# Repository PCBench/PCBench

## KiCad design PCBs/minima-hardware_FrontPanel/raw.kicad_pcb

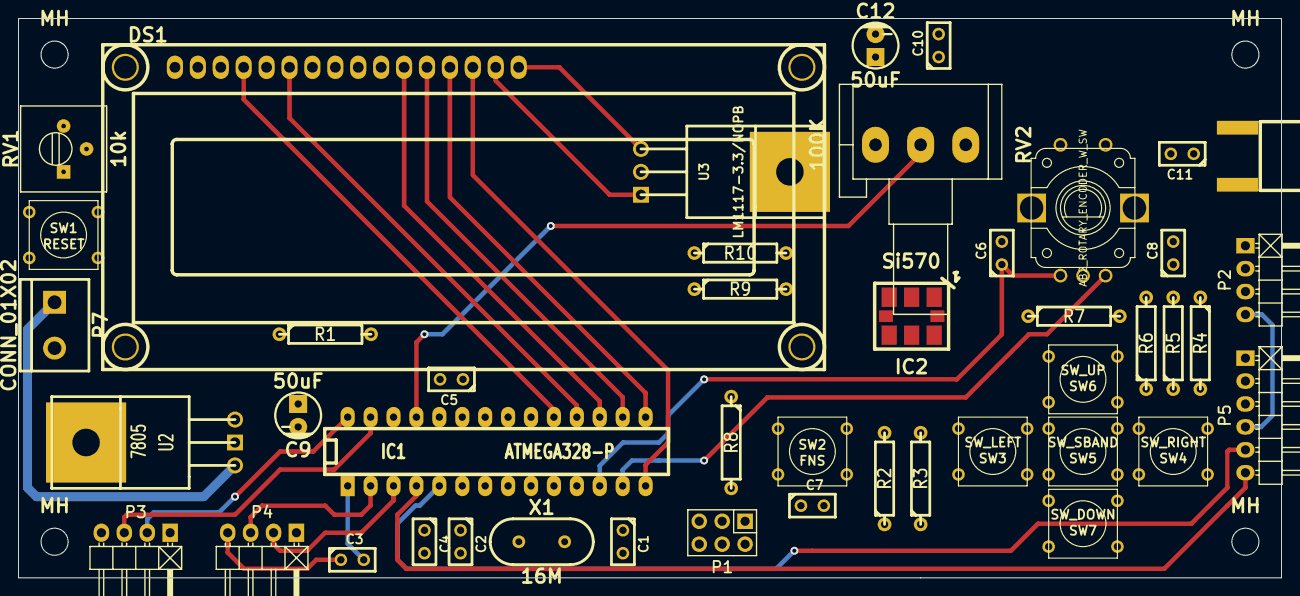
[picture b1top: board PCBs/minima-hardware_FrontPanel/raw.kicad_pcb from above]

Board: 2 copper layers, 140.0 x 62.0 mm, 49 parts (0 on the bottom side), 39 nets.

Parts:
C1, C2: 22pF; C1
C3: 0.1; C1
C4, C5: C; C1
C6, C7, C8: 1nF; C1
C9, C12: 50uF; Capacitor5x6RM2.5
C10, C11: .1uF; C1
DS1: LCD16X2; WC1602A
IC1: ATMEGA328-P; DIP-28__300_ELL
IC2: Si570; SI570_SI571_Standard
J1: sma; SMA_EDGE
MH: MountingHole_3mm_RevA_Date21Jun2010; MountingHole_3mm
MH#2, MH#3, MH#4: MountingHole_3mm_RevA_Date21Jun2010; MountingHole_3mm
P1: ICSP; Pin_Header_Straight_2x03
P2, P3, P4: CONN_01X04; Pin_Header_Angled_1x04
P5: CONN_01X06; Pin_Header_Angled_1x06
P7: CONN_01X02; bornier2
R1: 100K; R4
R2, R3, R4, R5, R6, R7: 4.7k; R4
R8: 47k; R4
R9, R10: 4.7K; R4
ROT_ENC1: AB2_ROTARY_ENCODER_W_SW; AB2_ROTARY_ENCODER_W_SWITCH
RV1: 10k; Potentiometer_Trimmer-Suntan-TSR-3386P
RV2: 100K; Potentiometer_Alps-RK16-single_largePads
SW1: RESET; SW_PUSH_SMALL
SW2: FNS; SW_PUSH_SMALL
SW3: SW_LEFT; SW_PUSH_SMALL
SW4: SW_RIGHT; SW_PUSH_SMALL
SW5: SW_SBAND; SW_PUSH_SMALL
SW6: SW_UP; SW_PUSH_SMALL
SW7: SW_DOWN; SW_PUSH_SMALL
U2: 7805; LM78XX
U3: LM1117-3.3/NOPB; TO220
X1: 16M; HC-49V

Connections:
+3.3V: C10.1, C12.1, IC2.6, P3.4, R9.1, R10.1, U3.3
+12V: P7.1, U2.VI
/D4: DS1.11, IC1.17, P1.4
/D5: DS1.12, IC1.16
/D6: DS1.13, IC1.15
/D7: DS1.14, IC1.14
/E: DS1.6, IC1.18, P1.1
/RS: DS1.4, IC1.19, P1.3
/TUNE: IC1.25, RV2.2
CWTONE: IC1.5, P5.5
GND: C1.2, C2.2, C4.2, C5.2, C6.2, C7.2, C8.2, C9.2, C10.2, C12.2, DS1.1, DS1.5, DS1.16, IC1.8, IC1.22, IC2.3, IC2.5, J1.2, P1.6, P2.1, P3.1, P4.1, P5.1, P7.2, ROT_ENC1.2, ROT_ENC1.4, RV1.1, RV2.1, SW1.2, SW2.2, SW3.2, SW4.2, SW5.2, SW6.2, SW7.2, U2.GND, U3.2
KEY: IC1.24, P5.2
unnamed: C1.1, IC1.10, X1.2
unnamed: C2.1, IC1.9, X1.1
unnamed: C3.2, IC1.1, P1.5, SW1.1
unnamed: C5.1, IC1.20, R1.2
unnamed: C6.1, IC1.12, ROT_ENC1.1
unnamed: C7.1, IC1.26, R2.2, R8.1, SW2.1
unnamed: C8.1, IC1.13, ROT_ENC1.3
unnamed: C11.1, J1.1
unnamed: C11.2, IC2.4
unnamed: DS1.3, RV1.2
unnamed: IC1.21, R8.2
unnamed: R2.1, R3.2, SW3.1
unnamed: R3.1, R4.2, SW4.1
unnamed: R4.1, R5.2, SW5.1
unnamed: R5.1, R6.2, SW6.1
unnamed: R6.1, R7.2, SW7.1
unnamed: R7.1, ROT_ENC1.6
PTT: IC1.23, P5.3
RF386: IC1.11, P2.3
RTS: C3.1, P4.4
RX: IC1.3, P4.2
SCL: IC1.28, IC2.8, P3.2, R10.2
SDA: IC1.27, IC2.7, P3.3, R9.2
TX: IC1.2, P4.3
TX/RX: IC1.6, P2.4, P5.4
USB/LSB: IC1.4, P5.6
VCC: C4.1, C9.1, DS1.2, DS1.15, IC1.7, P1.2, R1.1, RV1.3, RV2.3, U2.VO, U3.1

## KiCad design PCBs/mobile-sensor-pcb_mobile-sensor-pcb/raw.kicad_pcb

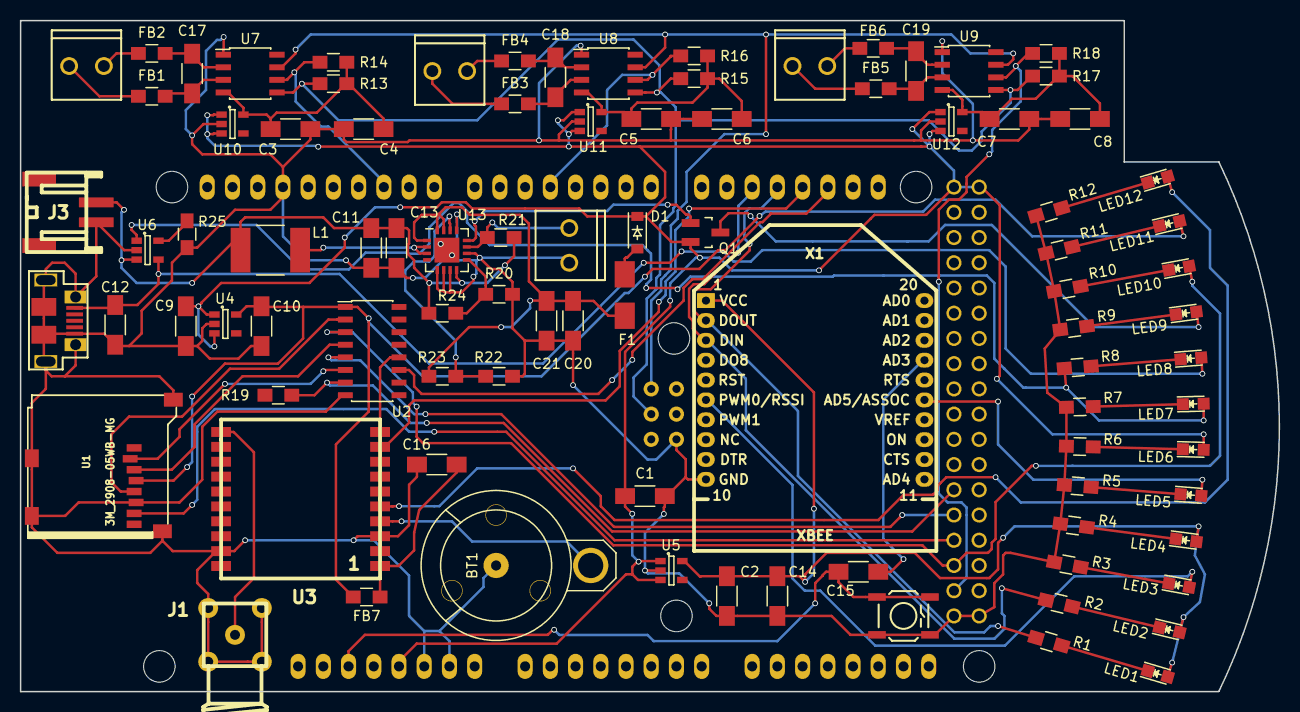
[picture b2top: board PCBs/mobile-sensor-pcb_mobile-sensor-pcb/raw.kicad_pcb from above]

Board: 2 copper layers, 126.8 x 67.6 mm, 93 parts (0 on the bottom side), 68 nets.

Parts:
BT1: Battery; CR1220
C1, C2, C3, C4, C5, C6, C7, C8, C9, C10, C11, C12: 10uF; C_1206_HandSoldering
C13, C14, C15, C16: 100nF; C_1206_HandSoldering
C17, C18, C19: 10nF; C_1206_HandSoldering
C20: 100uF; C_1206_HandSoldering
C21: 2.2uF; C_1206_HandSoldering
D1: MBR120VLSFT1G; SOD-123
F1: 500 mA fuse; Fuse_SMD1206_HandSoldering
FB1, FB2, FB3, FB4, FB5, FB6, FB7: FILTER; R_0805_HandSoldering
J1: SMA
J2: USB_OTG; USB-micro-B-female
J3: JST PH; s2b-ph-sm4-tb
L1: 6.8uH; Neosid_Inductor_SM-NE56_SMD2220
LED1: RX; LED-0805
LED2: TX; LED-0805
LED3: SIG; LED-0805
LED4, LED11: PWR; LED-0805
LED5: CONN; LED-0805
LED6: 5V; LED-0805
LED7: FULL; LED-0805
LED8: CHG; LED-0805
LED9: DEAD; LED-0805
LED10: LOG; LED-0805
LED12: FIX; LED-0805
Q1: PNP-BJT-BIASED_SOT; SOT-23_Handsoldering
R1, R2, R3, R4, R5, R6, R7, R8, R9, R10, R11, R12: 1K; R_0805_HandSoldering
R13, R14, R15, R16, R17, R18, R19: 10k; R_0805_HandSoldering
R20, R21: 340k; R_0805_HandSoldering
R22: 200k; R_0805_HandSoldering
R23, R24: 1.80M; R_0805_HandSoldering
R25: 2k; R_0805_HandSoldering
SHIELD1: ARDUINO_DUE_SHIELD
SW1: RESET; SW_PUSHBUTTON_SMD
SW2: ON/OFF; SCREWTERMINAL-3.5MM-2
TC1, TC2, TC3: SCREW TERMINAL; SCREWTERMINAL-3.5MM-2
U1: 3M_2908-05WB-MG
U2: 74HC4050; SOIC-16_3.9x9.9mm_Pitch1.27mm
U3: FGPMMOPA6H
U4: RT9193; SOT-23-5
U5: MIC5219; SOT-23-5
U6: MCP73831T-2ACI/OT; SOT-23-5
U7, U8, U9: MAX31855KASA; SOIC-8_3.9x4.9mm_Pitch1.27mm
U10, U11, U12: LP2980AIM5-3.3/NOPB; SOT-23-5
U13: TPS61030RSA; QFN-16-1EP_4x4mm_Pitch0.65mm
X1: XBEE; XBEE_PRO

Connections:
BATT-5V: C1.1, C9.1, D1.1, LED6.2, Q1.2, SHIELD1.5V, SHIELD1.5V_4, SHIELD1.5V_5, U4.1, U4.3, U5.1, U5.3, U10.1, U10.3, U11.1, U11.3, U12.1, U12.3
BATT-DEAD: LED9.2, Q1.3
BATT-STAT: LED7.2, R8.2, U6.1
GND: BT1.2, C1.2, C2.2, C3.2, C4.2, C5.2, C6.2, C7.2, C8.2, C9.2, C10.2, C11.2, C12.2, C13.2, C14.2, C16.2, C20.2, C21.2, J1.2, J1.3, J1.4, J1.5, J2.5, J2.6, J3.2, R3.2, R4.2, R5.2, R6.2, R7.2, R9.2, R10.2, R11.2, R12.2, R20.2, R22.2, R25.2, SHIELD1.GND1, SHIELD1.GND2, SHIELD1.GND3, SHIELD1.GND4, SHIELD1.GND5, SHIELD1.SP6, SW1.2, SW2.1, U1.6, U1.9, U2.8, U3.3, U3.19, U4.2, U5.2, U6.2, U7.1, U8.1, U9.1, U10.2, U11.2, U12.2, U13.5, U13.6, U13.7, U13.10, U13.13, U13.17, X1.10
GPS-3V3-RX: U2.12, U3.10
GPS-5V-RX: SHIELD1.19, U2.11
GPS-FIX: LED12.2, U3.5
GPS-SD-3V3: C10.1, FB7.1, LED11.2, U1.4, U2.1, U4.5
GPS-TX: SHIELD1.18, U3.9
unnamed: BT1.1, U3.4
unnamed: C3.1, C4.1, R13.1, R14.1, U7.4, U10.5
unnamed: C5.1, C6.1, R15.1, R16.1, U8.4, U11.5
unnamed: C7.1, C8.1, R17.1, R18.1, U9.4, U12.5
unnamed: C11.1, C13.1, J3.1, L1.1, R21.2, R24.1, U6.3, U13.8
unnamed: C15.2, X1.17
unnamed: C16.1, FB7.2, U3.1
unnamed: C17.1, FB1.2, U7.3
unnamed: C17.2, FB2.2, U7.2
unnamed: C18.1, FB3.2, U8.3
unnamed: C18.2, FB4.2, U8.2
unnamed: C19.1, FB5.2, U9.3
unnamed: C19.2, FB6.2, U9.2
unnamed: C20.1, C21.1, F1.2, R23.1, U13.1, U13.15, U13.16
unnamed: D1.2, F1.1
unnamed: FB1.1, TC1.2
unnamed: FB2.1, TC1.1
unnamed: FB3.1, TC2.2
unnamed: FB4.1, TC2.1
unnamed: FB5.1, TC3.2
unnamed: FB6.1, TC3.1
unnamed: J1.1, U3.11
unnamed: L1.2, U13.2, U13.3
unnamed: LED1.1, R1.1
unnamed: LED2.1, R2.1
unnamed: LED3.1, R3.1
unnamed: LED4.1, R4.1
unnamed: LED5.1, R5.1
unnamed: LED6.1, R6.1
unnamed: LED7.1, R7.1
unnamed: LED8.1, R8.1
unnamed: LED9.1, R9.1
unnamed: LED10.1, R10.1
unnamed: LED11.1, R11.1
unnamed: LED12.1, R12.1
unnamed: Q1.1, U13.12
unnamed: R20.1, R24.2, U13.9
unnamed: R21.1, SW2.2, U13.11
unnamed: R22.1, R23.2, U13.14
unnamed: R25.1, U6.5
unnamed: U1.2, U2.6
unnamed: U1.3, U2.4
unnamed: U1.5, U2.2
SD-CLK: LED10.2, SHIELD1.50, U2.3
SD-CS: R19.2, SHIELD1.44, U2.7
SD-MISO: SHIELD1.48, U1.7
SD-MOSI: SHIELD1.46, U2.5
TC-CS0: R14.2, SHIELD1.10, U7.6
TC-CS1: R16.2, SHIELD1.4, U8.6
TC-CS2: R18.2, SHIELD1.52, U9.6
TC-MISO: SHIELD1.SP1, U7.7, U8.7, U9.7
TC-SCK: R13.2, R15.2, R17.2, SHIELD1.SP3, U7.5, U8.5, U9.5
USB-5V: C12.1, J2.1, LED8.2, U6.4
XBEE-3V3: C2.1, C14.1, LED1.2, LED2.2, LED4.2, U5.5, X1.1
XBEE-DIO5: LED5.2, X1.15
XBEE-RESET: C15.1, SHIELD1.RST, SW1.1
XBEE-RSSI: LED3.2, X1.6
XBEE-RX: R1.2, SHIELD1.17, X1.2
XBEE-TX: R2.2, SHIELD1.16, X1.3

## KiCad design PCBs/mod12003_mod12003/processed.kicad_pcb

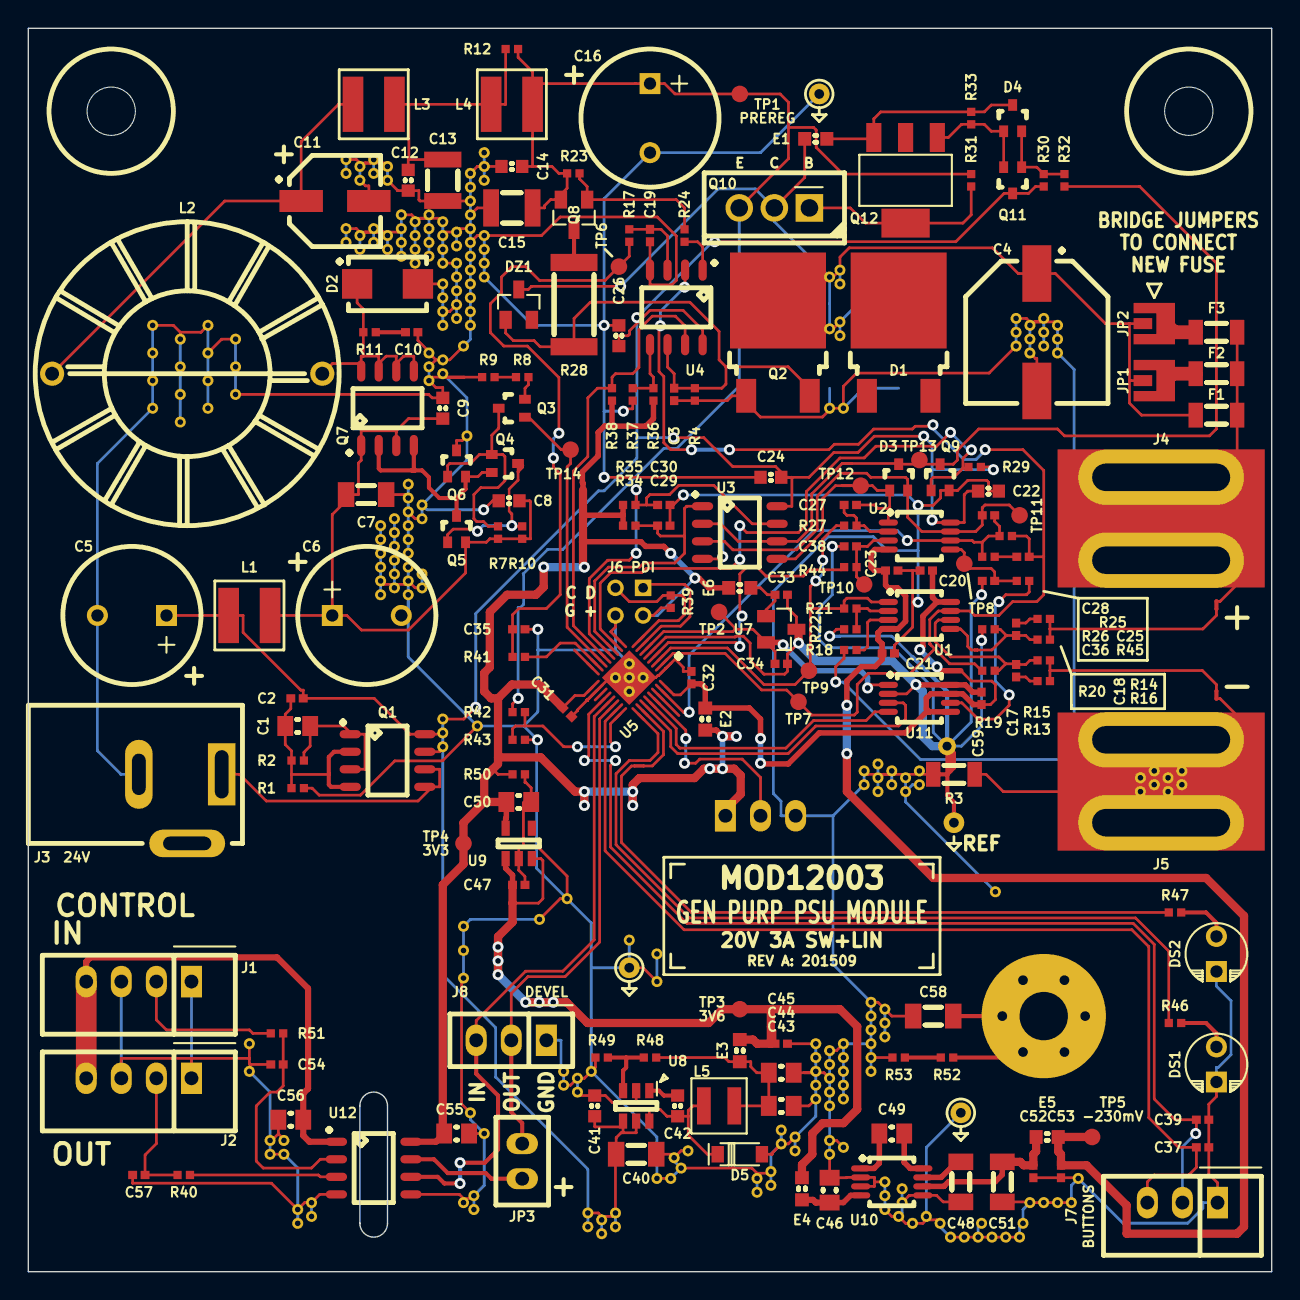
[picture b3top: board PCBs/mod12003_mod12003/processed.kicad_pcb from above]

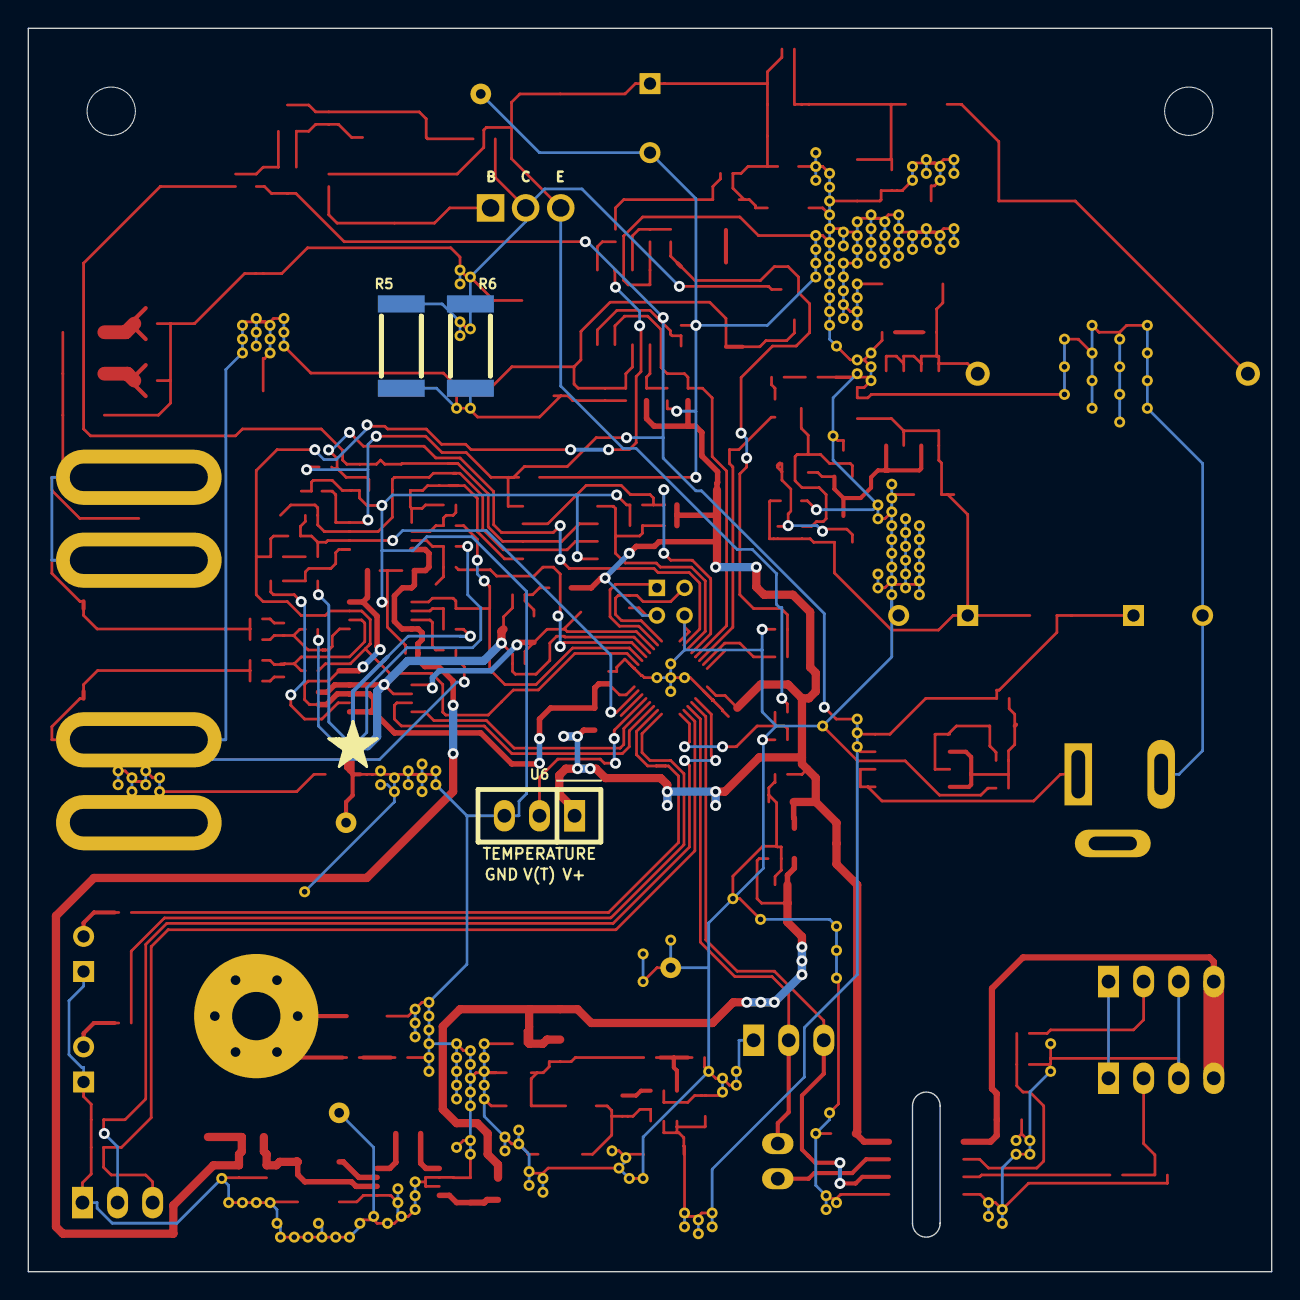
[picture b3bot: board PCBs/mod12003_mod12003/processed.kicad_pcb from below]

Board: 2 copper layers, 90.0 x 90.0 mm, 281 parts (3 on the bottom side), 97 nets.

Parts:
C1, C55, C56: 1u; CAPC2012X70
C2, C17, C18, C25, C27, C29, C30: 22n; CAPC1005X55
C3, C19, C20, C21, C23, C31, C32, C33, C34, C35, C36, C37, C38, C39, C45, C47, C52, C53, C59: 100n; CAPC1005X55
C4: 330u; CAPAE1030X1250
C5, C6, C16: 470u; C-ALUM-10mm
C7, C40: 6u8; CAPC3216X70
C8, C9, C12, C14, C22, C24, C26, C41, C42: 100n; CAPC1608X55
C10, C28, C54, C57: 220p; CAPC1005X55
C11: 33u; CAPAE660X570
C13, C15: 1u; CAPC3225X88
C43, C44, C46, C49, C50: 4u7; CAPC2012X70
C48, C51: 22u; CAPC3216X70
C58: 1n/1kV; CAPC3216X70
D1: 40V/5A; TO-252
D2: MBRS360B; DIOM5436X244
D3, D4: BAT54AWT; SC-70
D5: MBR0530; SOD-123
DS1: CV; LED-5mm
DS2: CC; LED-5mm
DZ1: 84B24; SOT-23
E1, E2, E3, E4, E5, E6: 120; INDC1608X95
F1, F2, F3: 4A; RESC3216X60
J1: IN; CONN-100MIL-M-1x4-SHROUD
J2: OUT; CONN-100MIL-M-1x4-SHROUD
J3: 24V; CONN-PJ-037A
J4: OUT+; J1
J5: OUT-; J1
J6: PDI; CONN-100MIL-M-2x3
J7: BUTTONS; CONN-100MIL-M-1x3-SHROUD
J8: DEVEL; CONN-100MIL-M-1x3
JP1, JP2: JUMPER-SOLDER; JUMPER-SOLDER-3mm
JP3: JUMPER; CONN-100MIL-M-1x2
L1, L3, L4: 3u3; BOURNS-SRN5040
L2: 100u; L1
L5: 22u; BOURNS-SRN3015
MP1, MP2, MP3: SCREW; SCREW-4-SUPPORTED
Q1, Q7: AO4805; SOIC127P600X175-8
Q2: 12A; TO-252
Q3, Q4: 3904; SC-70
Q5, Q6: 4403; SC-70
Q8: 4403; SOT-23
Q9: 2N7002PW; SC-70
Q10: D45H11; TO-220
Q11: PMSS3904; SC-70
Q12: PZT3904; SOT-223
R1, R2, R34, R35, R38, R41, R52, R53: 470k; RESC1005X40
R3: R010; RESC3216X60
R4, R22, R32, R37, R44, R45: 348; RESC1005X40
R5, R6, R28: 1k; RESC6432X70
R7, R15, R16, R21, R23, R24, R25, R29, R30, R39, R42: 22k; RESC1005X40
R8, R9, R10, R13, R14, R17, R18, R19, R20, R26, R27, R31, R33, R36, R43, R46, R47, R49, R50: 2k; RESC1005X40
R11, R12, R40, R51: 100; RESC1005X40
R48: 6k98; RESC1005X40
TP1: PREREG; TEST-SMD-SMALL
TP2: 2V048; TEST-SMD-SMALL
TP3: 3V6; TEST-SMD-SMALL
TP4: 3V3; TEST-SMD-SMALL
TP5: -230mV; TEST-SMD-SMALL
TP6: OVP_TH; TEST-SMD-SMALL
TP7: VSENSE; TEST-SMD-SMALL
TP8: VSET; TEST-SMD-SMALL
TP9: ISENSE; TEST-SMD-SMALL
TP10: ISET; TEST-SMD-SMALL
TP11: VDRIVE; TEST-SMD-SMALL
TP12: IDRIVE; TEST-SMD-SMALL
TP13: DRIVE; TEST-SMD-SMALL
TP14: SW; TEST-SMD-SMALL
U1: OPA2376AIDGK; SOP65P490X110-8
U2: LM358DGK; SOP65P490X110-8
U3, U4: LM393M; SOIC127P600X175-8
U5: ATXMEGA32E5-M4U; QFN40P400X400X55-33
U6: MCP9701-E/TO; CONN-100MIL-M-1x3
U7: ADR380; SOT-23
U8: AOZ1282; SOT-23-6
U9: TLV70233DBV; SOT-23-5
U10: LM7705; SOP65P490X110-8
U11: MAX5215; SOP65P490X110-8
U12: Si8421; SOIC127P600X175-8
VIA5, VIA5_2, VIA5_3, VIA5_4, VIA5_5, VIA5_6, VIA11, VIA12, VIA21, VIA22, VIA32, VIA311, VIA312, VIA321, VIA322, VIA331, VIA331_2, VIA331_3, VIA3111, VIA3111_2, VIA3111_3, VIA3112, VIA3112_2, VIA3112_3, VIA3112_4, VIA3112_5, VIA3112_6, VIA3112_7, VIA3112_8, VIA3112_9, VIA3112_10, VIA3112_11, VIA3112_12, VIA3112_13, VIA3112_14, VIA3112_15, VIA3112_16, VIA3112_17, VIA3121, VIA3121_2, VIA3122, VIA3122_2, VIA3311, VIA3312, VIA3313, VIA3321, VIA3322, VIA3323, VIA3331, VIA3332, VIA3333, VIA33111, VIA33112, VIA33113, VIA33114, VIA33115, VIA33121, VIA33122, VIA33123, VIA33124, VIA33125, VIA33131, VIA33132, VIA33133, VIA33134, VIA33135, VIA33211, VIA33212, VIA33212_2, VIA33212_3, VIA33212_4, VIA33212_5, VIA33221, VIA33222, VIA33223, VIA33231, VIA33232, VIA33233, VIA33241, VIA33242, VIA33243, VIA331111, VIA331112, VIA331311, VIA331312, VIA331313, VIA331321, VIA331322, VIA331323, VIA331331, VIA331332, VIA331333: VIA-0.8mm
W1, W2, W3: NET-TIE; NET-TIE-0.3mm

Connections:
3.3: C31.1, C50.1, C55.1, E2.1, E6.1, J6.2, R34.2, R35.2, R36.2, R38.2, R39.2, R50.1, TP4.1, U5.17, U6.1, U9.5, U12.8
3.6: C45.1, C47.1, E3.2, E4.1, TP3.1, U9.1, U9.3
+3.3A: C20.1, C32.1, C59.1, E2.2, U1.8, U5.32, U11.5, U11.7
/Control/BTN1: C39.1, J7.2, U5.20
/Control/BTN2: C37.1, J7.3, U5.23
/Control/FORCE_SAT_L: C28.2, R25.1, R26.1, U2.6, U5.31
/Control/ISENSE: R21.2, R27.2, TP9.1, U1.1, U5.3
/Control/ISET: C38.1, R44.1, TP10.1, U2.3
/Control/LEDCC: R46.1, U5.25
/Control/LEDCV: R47.1, U5.26
/Control/OVPTH_PWM: R41.2, U5.15
/Control/OVP_THRESH: C35.1, R17.2, R41.1, TP6.1
/Control/PDI_C: J6.5, R39.1, U5.8
/Control/PDI_D: J6.1, U5.7
/Control/PREREG_SW: Q3.1, TP14.1, U5.14
/Control/RX: J8.2, JP3.2, U5.22
/Control/SCL: U5.27, U11.3
/Control/SDA: U5.28, U11.4
/Control/TEMP: U5.29, U6.2
/Control/VREF: C34.1, TP2.1, U5.6, U7.2, U11.1
/Control/VSENSE: C25.2, R19.1, R25.2, TP7.1, U1.7, U4.2, U5.2
/Control/VSET: C36.1, R45.1, TP8.1, U2.5
/Control/~EN: Q9.1, R29.1, U5.10
/Control/~ILIM: C30.2, R35.1, U3.7, U5.12
/Control/~SCR_TRIPPED: R38.1, U4.7, U5.13
/Control/~VLIM: C29.2, R34.1, U3.1, U5.11
/Iso/FROM_ISO_IN: JP3.1, U12.7
/Iso/ISO_5V: C56.1, J1.4, J2.4, U12.1
/Iso/ISO_GND: C54.1, C56.2, C57.1, J1.1, J1.3, J2.1, J2.3, U12.4, VIA3112_8.1, VIA3112_9.1, VIA3112_10.1, VIA3112_11.1, VIA3112_12.1, VIA3112_13.1, VIA3112_14.1, VIA3112_15.1, VIA3112_16.1, VIA3112_17.1
/Iso/ISO_IN: J1.2, R51.2
/Iso/ISO_OUT: C57.2, J2.2, R40.2
/Iso/TO_ISO_OUT: J8.3, U5.21, U12.6
/Linear/ISENSE: C3.2, C4.2, J5.1, Q2.1, R3.1, R4.1, R5.1, R6.1, R18.2, W3.2
/Linear/P_IN: C14.2, C15.1, C16.1, L4.1, Q8.2, Q10.3, R12.1, R23.2, R31.2, R42.1, TP1.1
/Linear/P_OUT: C4.1, DZ1.3, E1.1, F1.2, JP1.1, JP2.1, Q2.3, Q10.2, R5.2, R6.2, VIA5.1, VIA5_2.1, VIA5_3.1, VIA5_4.1, VIA5_5.1, VIA5_6.1
/Linear/SCR_FIRE: C3.1, DZ1.1, Q2.2, R4.2, R28.1, U4.6
/Linear/VSENSE+: R14.2, R16.2, W2.1
/Linear/VSENSE-: R13.2, R15.2, W3.1
/LocalPwr/3V6SW: C42.2, D5.1, L5.2, U8.6
/LocalPwr/3V6UF: C43.1, C44.1, E3.1, L5.1, R48.1
/LocalPwr/3V6_7705: C46.1, E4.2, U10.4
/LocalPwr/CF+: C49.2, U10.1
/LocalPwr/CF-: C49.1, U10.8
/OUT+: F1.1, F2.1, F3.1, J4.1, W2.2
/PAD_MP1: C58.1, MP1.1, R52.2
/Preregulator/PREF1: C11.1, L2.1, L3.2
/Preregulator/PREF2: C12.2, C13.1, L3.1, L4.2, R12.2
/Preregulator/SWNODE: D2.1, L2.2, Q7.5, Q7.6, Q7.7, Q7.8, R11.2
/Preregulator/V+F: C6.1, C7.1, C8.2, C9.2, L1.1, Q5.2, Q7.1, Q7.3, R7.1, R10.1
/VIN: J3.1, Q1.5, Q1.6
/VRP: C1.1, Q1.1, Q1.3, R2.2
GND: C5.2, C6.2, C7.2, C8.1, C9.1, C10.1, C11.2, C12.1, C13.2, C14.1, C15.2, C16.2, C19.2, C20.2, C21.2, C22.1, C23.2, C24.1, C26.1, C29.1, C30.1, C31.2, C32.2, C35.2, C37.2, C39.2, C40.2, C41.2, C43.2, C44.2, C45.2, C46.2, C47.2, C48.2, C50.2, C51.2, C52.2, C53.2, C55.2, C58.2, D2.2, D5.2, DS1.1, DS2.1, J3.2, J6.6, J7.1, J8.1, Q6.3, Q9.2, R1.1, R3.2, R9.2, R37.1, R43.2, R49.2, R50.2, R53.1, U3.4, U4.4, U5.1, U5.9, U5.18, U5.33, U6.3, U8.2, U9.2, U10.2, U10.3, U10.5, U12.5, VIA11.1, VIA12.1, VIA21.1, VIA22.1, VIA32.1, VIA311.1, VIA312.1, VIA321.1, VIA322.1, VIA331.1, VIA331_2.1, VIA331_3.1, VIA3111.1, VIA3111_2.1, VIA3111_3.1, VIA3112.1, VIA3112_2.1, VIA3112_3.1, VIA3112_4.1, VIA3112_5.1, VIA3112_6.1, VIA3112_7.1, VIA3121.1, VIA3121_2.1, VIA3122.1, VIA3122_2.1, VIA3311.1, VIA3312.1, VIA3313.1, VIA3321.1, VIA3322.1, VIA3323.1, VIA3331.1, VIA3332.1, VIA3333.1, VIA33111.1, VIA33112.1, VIA33113.1, VIA33114.1, VIA33115.1, VIA33121.1, VIA33122.1, VIA33123.1, VIA33124.1, VIA33125.1, VIA33131.1, VIA33132.1, VIA33133.1, VIA33134.1, VIA33135.1, VIA33211.1, VIA33212.1, VIA33212_2.1, VIA33212_3.1, VIA33212_4.1, VIA33221.1, VIA33222.1, VIA33223.1, VIA33231.1, VIA33232.1, VIA33233.1, VIA33241.1, VIA33242.1, VIA33243.1, VIA331111.1, VIA331112.1, VIA331311.1, VIA331312.1, VIA331313.1, VIA331321.1, VIA331322.1, VIA331323.1, VIA331331.1, VIA331332.1, VIA331333.1, W1.1
unnamed: C1.2, C2.2, Q1.2, Q1.4, R1.2, R2.1
unnamed: C10.2, R11.1
unnamed: C17.1, R15.1, R19.2, U1.6
unnamed: C17.2, R13.1
unnamed: C18.1, R16.1, R20.2, U1.5
unnamed: C18.2, R14.1
unnamed: C19.1, R17.1, U4.3
unnamed: C25.1, R26.2
unnamed: C27.1, D3.1, TP12.1, U2.1, U3.5
unnamed: C27.2, R27.1, U2.2
unnamed: C28.1, D3.2, TP11.1, U2.7, U3.3
unnamed: C33.1, E6.2, U7.1
unnamed: C42.1, U8.1
unnamed: C48.1, U10.7
unnamed: C51.1, C52.1, E5.1, U10.6
unnamed: C54.2, R51.1, U12.2
unnamed: D3.3, Q9.3, R32.1, TP13.1, U3.2, U3.6
unnamed: D4.1, Q11.2, Q12.1, R33.2
unnamed: D4.2, Q11.1, R30.1, R32.2
unnamed: D4.3, E1.2, Q12.3, R33.1
unnamed: DS1.2, R46.2
unnamed: DS2.2, R47.2
unnamed: F2.2, JP1.2
unnamed: F3.2, JP2.2
unnamed: Q3.2, R8.1
unnamed: Q3.3, Q4.1, Q6.1, R7.2
unnamed: Q4.2, Q5.3, Q6.2, Q7.2, Q7.4
unnamed: Q4.3, Q5.1, R10.2
unnamed: Q8.1, R23.1, R24.2
unnamed: Q8.3, R28.2
unnamed: Q10.1, Q12.4, R31.1
unnamed: R8.2, R9.1
unnamed: R18.1, U1.3
unnamed: R21.1, R22.2, U1.2
unnamed: R24.1, U4.1
unnamed: R36.1, R37.2, U4.5
unnamed: R40.1, U12.3
unnamed: R42.2, R43.1, U5.24
unnamed: R44.2, U5.4
unnamed: R45.2, U11.6
unnamed: R48.2, R49.1, U8.3
unnamed: R52.1, R53.2
REFGND: C33.2, C34.2, C36.2, C38.2, C59.2, R20.1, R22.1, U5.5, U7.3, U11.2, U11.8, VIA33212_5.1, W1.2
V+: C2.1, C5.1, C22.2, C24.2, C26.2, C40.1, C41.1, L1.2, Q1.7, Q1.8, Q11.3, R29.2, R30.2, U2.8, U3.8, U4.8, U8.4, U8.5
V-: C21.1, C23.1, C53.1, E5.2, TP5.1, U1.4, U2.4

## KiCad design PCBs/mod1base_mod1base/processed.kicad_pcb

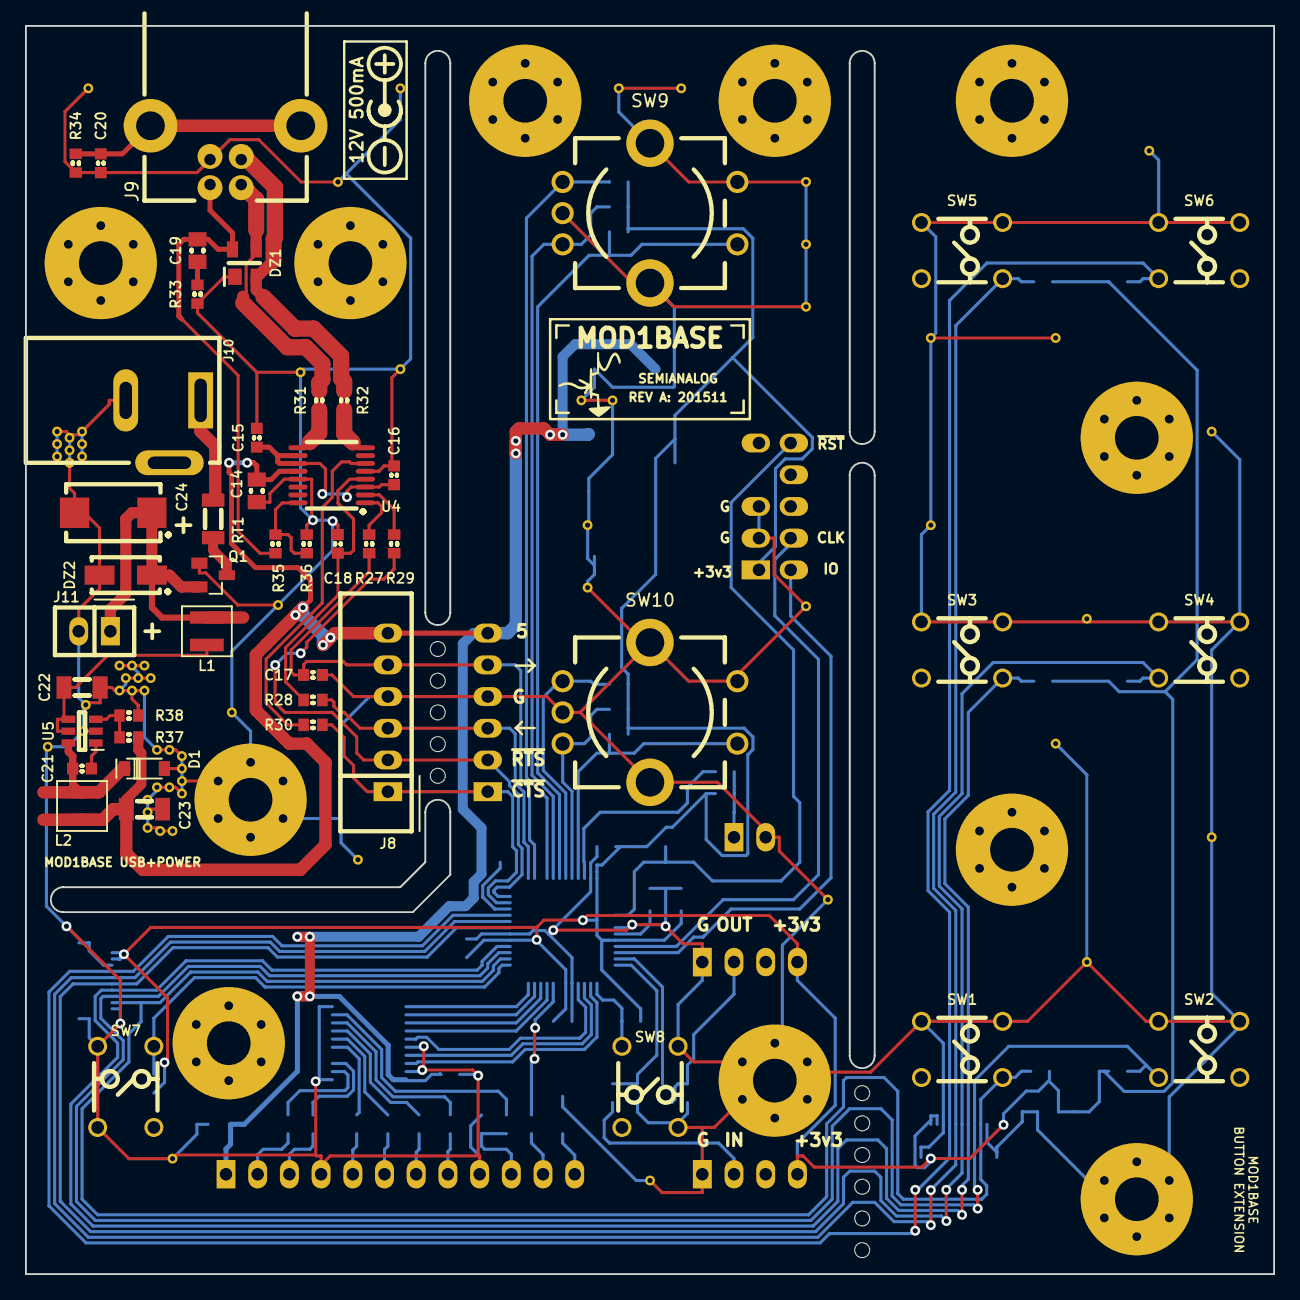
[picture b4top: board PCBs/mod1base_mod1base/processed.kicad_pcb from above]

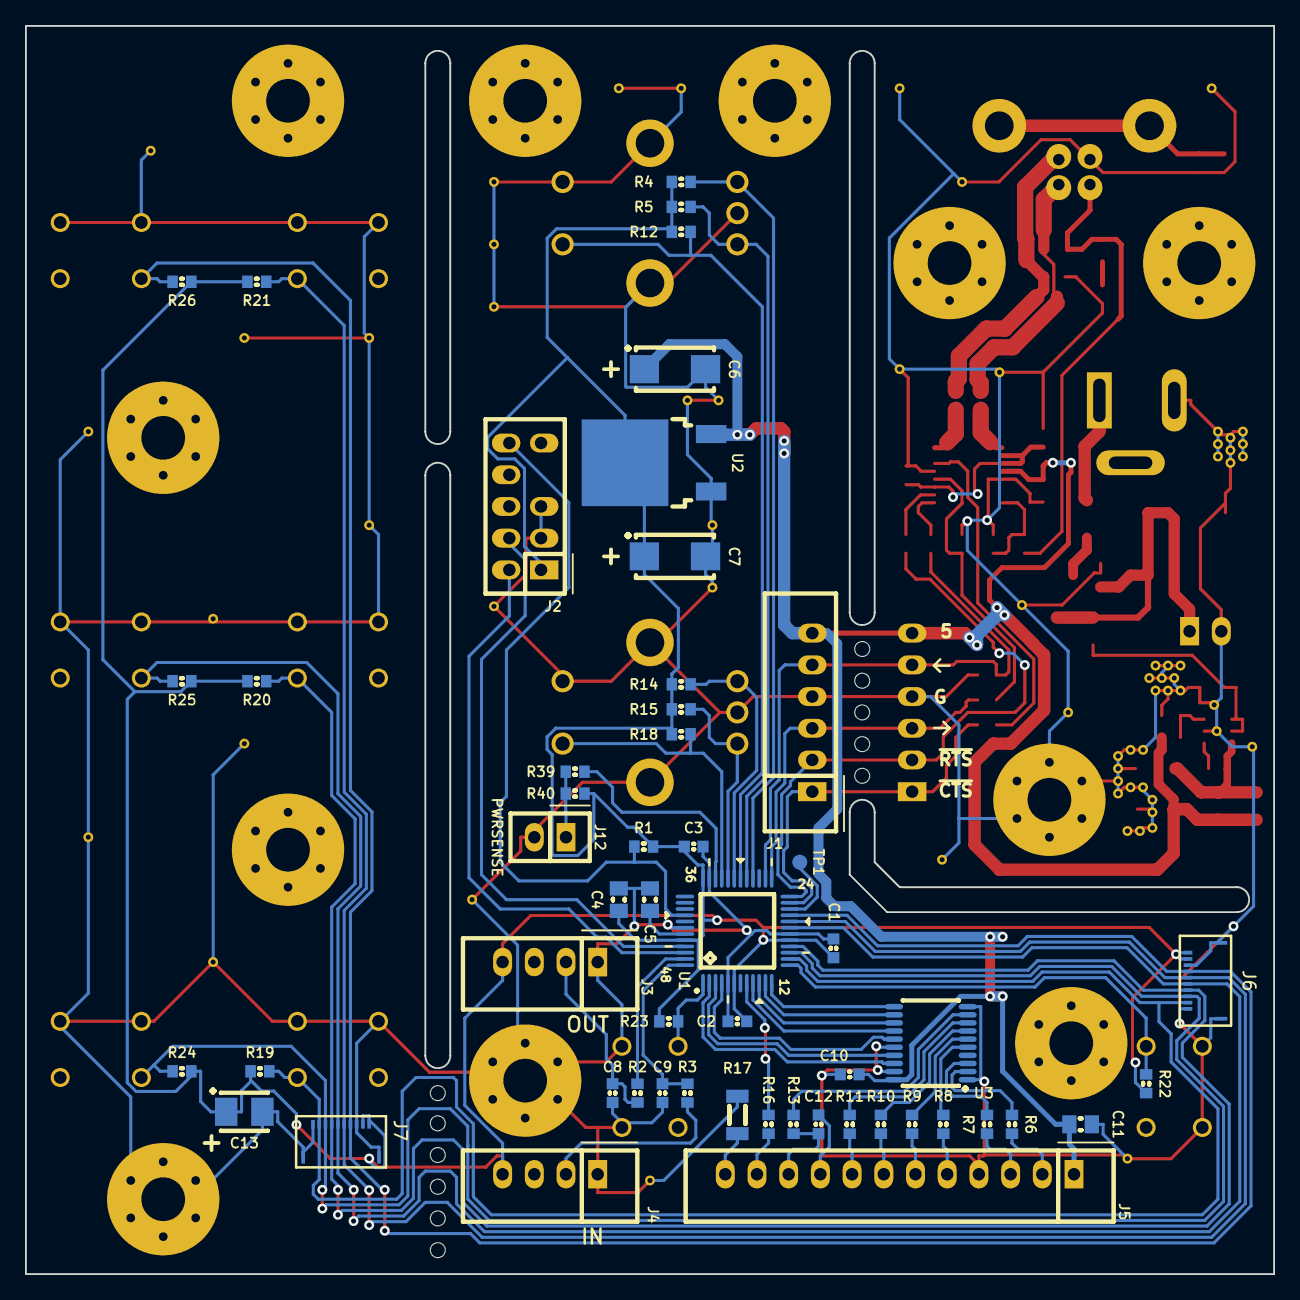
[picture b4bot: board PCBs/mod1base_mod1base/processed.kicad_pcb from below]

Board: 2 copper layers, 100.0 x 100.0 mm, 110 parts (53 on the bottom side), 76 nets.

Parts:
C1, C2, C3, C10, C12, C15, C16, C21: 100n; CAPC1608X55
C4, C5, C11, C14, C19: 2u2; CAPC2012X70
C6, C7: 10u/25; CAPMP6032X280
C8, C9, C17, C18, C20: 220p; CAPC1608X55
C13: 6u8/10; CAPMP3528X210
C22, C23: 22u; CAPC3216X70
C24: 22u/25; CAPMP7343X310
D1: MBR0520; SOD-123
DZ1: DRTR5V0U2SR; SOT-143
DZ2: 1SMA5929BT3G; DIOM5226X203
J1, J8: COM; CONN-100MIL-M-1x6-SHROUD
J2: SWD; CONN-100MIL-M-2x5
J3: OUT; CONN-100MIL-M-1x4-SHROUD
J4: IN; CONN-100MIL-M-1x4-SHROUD
J5: LCD; CONN-100MIL-M-1x12-SHROUD
J6, J7: 5034801000; FFC
J9: USB; CONN-61729
J10: 12V 500mA; CONN-PJ-037A
J11: FAN; CONN-100MIL-M-1x2
J12: PWRSENSE; CONN-100MIL-M-1x2
L1, L2: 6u8; BOURNS-SRN3015
MP1, MP2, MP3, MP4, MP5, MP6, MP7, MP8, MP9, MP10, MP11: SCREW; SCREW-4-SUPPORTED
Q1: IRLML6402; SOT-23
R1, R4, R5, R12, R13, R14, R15, R16, R18, R19, R20, R21, R22, R23, R24, R25, R26, R35, R39, R40: 4k7; RESC1608X50
R2, R3, R6, R7, R8, R9, R10, R11, R27, R28, R29, R30: 100; RESC1608X50
R17: TBD; RESC3216X60
R31, R32, R33: 27; RESC1608X50
R34, R36, R37: 10k; RESC1608X50
R38: 1k91; RESC1608X50
RT1: 750mA; RESC3216X60
SW1: SOFT1; ESWITCH-TL1105
SW2: PRESETS; ESWITCH-TL1105
SW3, SW4: SOFT2; ESWITCH-TL1105
SW5: SOFT3; ESWITCH-TL1105
SW6: ALL_LOAD; ESWITCH-TL1105
SW7, SW8: STORE; ESWITCH-TL1105
SW9, SW10: EVE-JBBF2020B; PANASONIC-EVEJB
TP1: EXTRA; TEST-SMD-SMALL
U1: ATSAMD20G18A-AU; QFP50P900X900X120-48
U2: LM1117DT-3.3; TO-252
U3: 74HCT245PW; SOP65P640X110-20
U4: FT230XS; SOP63P600X160-16
U5: AP3211; SOT-23-6

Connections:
3.3: C1.1, C2.1, C3.1, C4.1, C7.1, C13.1, J2.1, J3.4, J4.4, J6.9, J6.10, J7.9, J7.10, R1.1, R4.2, R5.2, R12.2, R14.2, R15.2, R18.2, R19.2, R20.2, R21.2, R22.2, R23.2, R24.2, R25.2, R26.2, R40.1, U1.6, U1.17, U1.36, U1.44, U2.3
5: C6.1, C10.1, C11.1, C14.1, C23.1, J1.6, J5.1, J8.6, L2.1, R37.1, U2.2, U3.20, U4.12
12: C24.1, DZ2.1, J11.1, L1.2, Q1.2
+3.3A: C15.1, C16.1, U4.3, U4.10, U4.11
/COM_IN: C9.1, R3.2, U1.48
/COM_OUT: R2.2, U1.47
/PWRSENSE: R39.2, U1.34
/Panel/5VLCD_CONT: C12.1, J5.10, R13.2
/Panel/5VLCD_D4: J5.5, R8.1
/Panel/5VLCD_D5: J5.6, R9.1
/Panel/5VLCD_D6: J5.7, R10.1
/Panel/5VLCD_D7: J5.8, R11.1
/Panel/5VLCD_D_~C: J5.2, R6.1
/Panel/5VLCD_E: J5.3, R7.1
/Panel/5VLCD_LEDK: J5.12, R17.1
/Panel/5VVFD_BUSY: J5.11, R16.2
/Panel/LCD_CONT: U1.12, U3.11
/Panel/LCD_D4: U1.4, U3.15
/Panel/LCD_D5: U1.9, U3.14
/Panel/LCD_D6: U1.10, U3.13
/Panel/LCD_D7: U1.11, U3.12
/Panel/LCD_D_~C: U1.2, U3.18
/Panel/LCD_E: U1.3, U3.17
/Panel/VFD_BUSY: R16.1, U1.8
/ROT0: R5.1, SW9.1, U1.29
/ROT1: R4.1, SW9.3, U1.28
/ROT2: R12.1, SW9.4, U1.30
/ROT3: R15.1, SW10.1, U1.32
/ROT4: R14.1, SW10.3, U1.31
/ROT5: R18.1, SW10.4, U1.33
/Rear breakaway/5VFB: R37.2, R38.1, U5.3
/Rear breakaway/5VIN: C22.1, L1.1, U5.4, U5.5
/Rear breakaway/5VSW: C21.1, D1.1, L2.2, U5.6
/Rear breakaway/D+: R32.1, U4.8
/Rear breakaway/D-: R31.1, U4.9
/Rear breakaway/FROM_USB: C17.1, J1.5, J8.5, R27.1, U1.26
/Rear breakaway/TO_USB: J1.3, J8.3, R28.1, U1.25
/Rear breakaway/USBD+: DZ1.2, J9.3, R32.2
/Rear breakaway/USBD-: DZ1.3, J9.2, R31.2
/Rear breakaway/VBSENSE_FTDI: R35.2, R36.1, U4.16
/Rear breakaway/~CTS: J1.1, J8.1, R30.1, U1.23
/Rear breakaway/~RTS: J1.2, J8.2, R29.1, U1.24
/SW1: J6.2, J7.2, R19.1, SW1.3, U1.14
/SW2: J6.3, J7.3, R24.1, SW2.1, U1.15
/SW3: J6.4, J7.4, R20.1, SW3.3, U1.16
/SW4: J6.5, J7.5, R25.1, SW4.1, U1.19
/SW5: J6.6, J7.6, R21.1, SW5.3, U1.20
/SW6: J6.7, J7.7, R26.1, SW6.1, U1.21
/SW7: R22.1, SW7.3, U1.13
/SW8: R23.1, SW8.1, U1.1
/SWCLK: J2.4, U1.45
/SWDIO: J2.2, U1.46
/VCORE: C5.1, U1.43
/~RST: J2.10, R1.2, U1.40
GND: C1.2, C2.2, C3.2, C4.2, C5.2, C6.2, C7.2, C8.2, C9.2, C10.2, C11.2, C12.2, C13.2, C14.2, C15.2, C16.2, C17.2, C18.2, C20.2, C22.2, C23.2, C24.2, D1.2, DZ1.1, DZ2.2, J1.4, J2.3, J2.5, J3.1, J4.1, J5.4, J5.9, J6.1, J6.8, J7.1, J7.8, J8.4, J9.4, J10.2, J11.2, J12.2, MP2.1, MP5.1, MP11.1, Q1.1, R17.2, R33.1, R34.2, R36.2, R38.2, SW1.2, SW1.4, SW2.2, SW2.4, SW3.2, SW3.4, SW4.2, SW4.4, SW5.2, SW5.4, SW6.2, SW6.4, SW7.2, SW7.4, SW8.2, SW8.4, SW9.2, SW9.5, SW10.2, SW10.5, U1.5, U1.18, U1.35, U1.42, U2.1, U3.1, U3.10, U3.16, U3.19, U4.5, U4.13, U5.2
unnamed: C8.1, J3.2, R2.1
unnamed: C18.1, R28.2, U4.4
unnamed: C19.2, R33.2
unnamed: C20.1, J9.SH, R34.1
unnamed: C21.2, U5.1
unnamed: J4.2, R3.1
unnamed: J10.1, RT1.2
unnamed: J12.1, R39.1, R40.2
unnamed: Q1.3, RT1.1
unnamed: R6.2, U3.2
unnamed: R7.2, U3.3
unnamed: R8.2, U3.5
unnamed: R9.2, U3.6
unnamed: R10.2, U3.7
unnamed: R11.2, U3.8
unnamed: R13.1, U3.9
unnamed: R27.2, U4.1
unnamed: R29.2, U4.2
unnamed: R30.2, U4.6
unnamed: TP1.1, U1.22
VBUS: C19.1, DZ1.4, J9.1, R35.1

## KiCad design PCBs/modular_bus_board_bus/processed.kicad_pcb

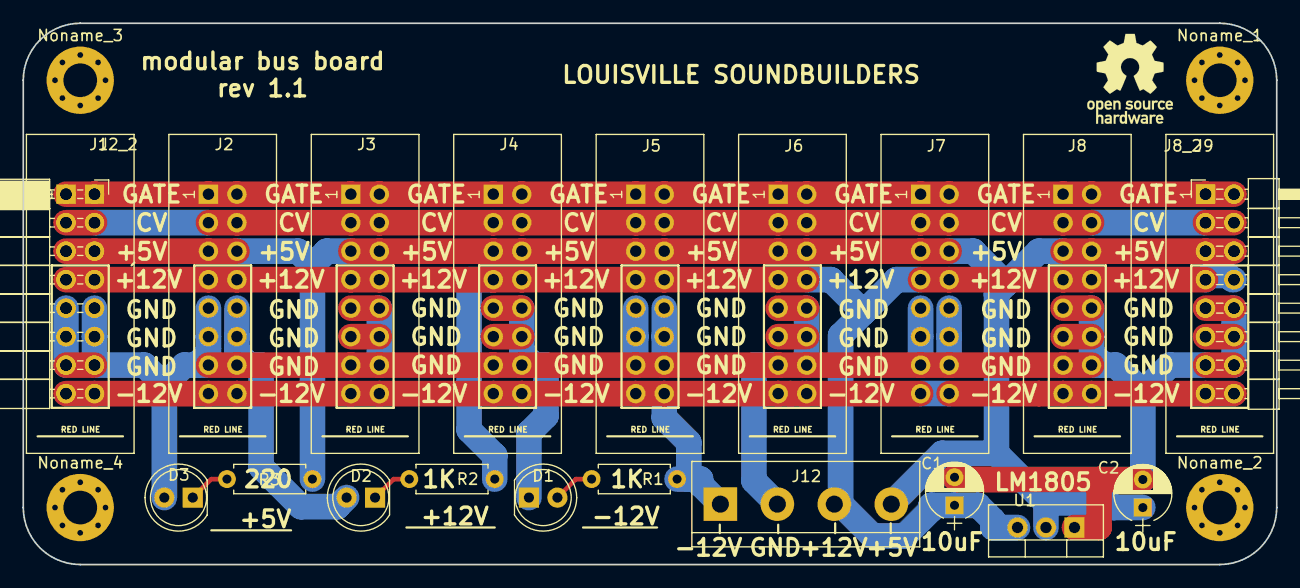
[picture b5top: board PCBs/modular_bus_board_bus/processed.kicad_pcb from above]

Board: 2 copper layers, 111.8 x 48.3 mm, 25 parts (0 on the bottom side), 9 nets.

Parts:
C1, C2: CP; CP_Radial_D5.0mm_P2.50mm
D1, D2, D3: LED; LED_D5.0mm
J1: CONN_02X08; Socket_Strip_Angled_2x08_Pitch2.54mm
J2, J2_2, J3, J4, J5, J6, J7, J8, J8_2: CONN_02X08; IDC_Header_Straight_16pins
J9: CONN_02X08; Pin_Header_Angled_2x08_Pitch2.54mm
J12: Screw_Terminal_1x04; bornier4
Noname_1, Noname_2, Noname_3, Noname_4: MountingHole_3mm_Pad_Via
R1, R2: 1K; R_Axial_DIN0207_L6.3mm_D2.5mm_P7.62mm_Horizontal
R3: 220; R_Axial_DIN0207_L6.3mm_D2.5mm_P7.62mm_Horizontal
U1: LM1085; TO-220_Vertical

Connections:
+5V: C2.1, J1.5, J1.6, J2.5, J2.6, J2_2.5, J2_2.6, J3.5, J3.6, J4.5, J4.6, J5.5, J5.6, J6.5, J6.6, J7.5, J7.6, J8.5, J8.6, J8_2.5, J8_2.6, J9.5, J9.6, J12.4, R3.2, U1.2
+12V: C1.1, J1.7, J1.8, J2.7, J2.8, J2_2.7, J2_2.8, J3.7, J3.8, J4.7, J4.8, J5.7, J5.8, J6.7, J6.8, J7.7, J7.8, J8.7, J8.8, J8_2.7, J8_2.8, J9.7, J9.8, J12.3, R2.2, U1.3
-12V: J1.15, J1.16, J2.15, J2.16, J2_2.15, J2_2.16, J3.15, J3.16, J4.15, J4.16, J5.15, J5.16, J6.15, J6.16, J7.15, J7.16, J8.15, J8.16, J8_2.15, J8_2.16, J9.15, J9.16, J12.1, R1.2
CV: J1.3, J1.4, J2.3, J2.4, J2_2.3, J2_2.4, J3.3, J3.4, J4.3, J4.4, J5.3, J5.4, J6.3, J6.4, J7.3, J7.4, J8.3, J8.4, J8_2.3, J8_2.4, J9.3, J9.4
GATE: J1.1, J1.2, J2.1, J2.2, J2_2.1, J2_2.2, J3.1, J3.2, J4.1, J4.2, J5.1, J5.2, J6.1, J6.2, J7.1, J7.2, J8.1, J8.2, J8_2.1, J8_2.2, J9.1, J9.2
GND: C1.2, C2.2, D1.1, D2.2, D3.2, J1.9, J1.10, J1.11, J1.12, J1.13, J1.14, J2.9, J2.10, J2.11, J2.12, J2.13, J2.14, J2_2.9, J2_2.10, J2_2.11, J2_2.12, J2_2.13, J2_2.14, J3.9, J3.10, J3.11, J3.12, J3.13, J3.14, J4.9, J4.10, J4.11, J4.12, J4.13, J4.14, J5.9, J5.10, J5.11, J5.12, J5.13, J5.14, J6.9, J6.10, J6.11, J6.12, J6.13, J6.14, J7.9, J7.10, J7.11, J7.12, J7.13, J7.14, J8.9, J8.10, J8.11, J8.12, J8.13, J8.14, J8_2.9, J8_2.10, J8_2.11, J8_2.12, J8_2.13, J8_2.14, J9.9, J9.10, J9.11, J9.12, J9.13, J9.14, J12.2, U1.1
unnamed: D1.2, R1.1
unnamed: D2.1, R2.1
unnamed: D3.1, R3.1

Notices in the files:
PCBs/moonpunchorg_pcieduino/processed.kicad_pcb:
CC-BY-SA 3.0
